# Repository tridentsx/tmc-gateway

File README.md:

# tmc-gateway

A PoE Ethernet- and USB-attached GPIB instrument gateway: one small board,
plugged directly into an instrument's IEEE-488 connector, that exposes it to
the network and to USB simultaneously.

## What it does

One RP2354A-based adapter per GPIB instrument, acting as that instrument's
GPIB System Controller and Controller-in-Charge, reachable over:

- **[HiSLIP][hislip]** (IVI-6.1) over Ethernet/PoE, TCP port 4880
- **USBTMC** and its **USB488** subclass over USB
- Raw SCPI over TCP port 5025 (planned; not yet built)

The central architectural rule, carried over from the design specification:

> HiSLIP, USBTMC/USB488, raw SCPI, and any future management interface never
> manipulate GPIB pins directly. They submit operations to one serialized
> GPIB engine.

That engine is [`gpib.Instrument`](gpib/instrument.go) — see
[Software](#software) below.

## Hardware

| | |
|---|---|
| MCU | RP2354A (RP2350 family, 2 MB integrated flash), QFN-60 |
| Ethernet | WIZnet W5500 (SPI) |
| PoE | DP9900LPB isolated PD module, IEEE 802.3af, with a USB-C alternate power path (§30.1) |
| GPIB transceivers | TI SN75160B (data bus) + SN75161B (management bus) |
| GPIB connector | 24-pin IEEE-488, NorComp 112-024-113R001 |
| USB | USB-C (USBTMC/USB488, plus alternate power input) |

Board is 62×68 mm, 4 copper layers. Schematic is complete and verified —
confirmed by actually running the checks below, not just citing an old note:
`scripts/netlist-check.py` reports **124 checks, 0 failures**; ERC reports 3
`pin_not_driven` errors, all on W5500 (`U2`) SPI inputs (`SCS`/`SCLK`/`MOSI`)
flagged because the driving RP2354A pins are bidirectional across a
hierarchical sheet link — a severity-policy question, not a wiring defect.
PCB has all 93 footprints placed but is **not yet routed**.

- [`docs/design-spec.md`](docs/design-spec.md) — the master design
  specification. One document by design: Part I is the HiSLIP library
  ([tridentsx/hislip][hislip], developed in that separate repository), Part
  II is this hardware, Part III is this firmware, and Parts IV–VII
  (milestones, acceptance criteria, design decisions, risk register) span
  all three. Source comments in `hislip` cite it by section, e.g. "§5.1".
- [`docs/netlist-spec.md`](docs/netlist-spec.md) / [`docs/netlist-spec.nets`](docs/netlist-spec.nets) —
  the canonical net table `scripts/netlist-check.py` verifies the exported
  schematic netlist against.
- [`docs/rp2354a-pinmap.md`](docs/rp2354a-pinmap.md) — the RP2354A GPIO
  assignment: 8 data lines and the DAV/NDAC/NRFD handshake lines suggested
  for PIO, ATN/SRQ/REN/IFC/EOI as plain GPIO, SPI0 to the W5500.

## Software

```text
gpib/            the Instrument abstraction every front end drives (no
                  firmware, no bus driver -- just the interface)
hislipfront/      adapts gpib.Instrument to tridentsx/hislip's server.Device
usbtmcfront/      adapts gpib.Instrument to USBTMC/USB488 Bulk-OUT messages
usbep/            portable, unit-tested USB packet reassembly (host->device)
                  and chunking (device->host) usbtmcfront's messages ride on
cmd/firmware/     the real (skeleton) RP2354A firmware entry point --
                  tinygo-only, gated by the "tinygo" build tag
cmd/tinygocheck/  not firmware -- exists so `just tinygo` has a real main
                  package to build and link, exercising gpib/hislipfront/
                  usbtmcfront together under mainline go's dependency
                  graph but a real tinygo build
cmd/debugconsole/ host-side only (plain go build, no tinygo tag): a
                  terminal UI for cmd/firmware's CDC debug console
```

`gpib.Instrument` is deliberately not a copy of `hislip/server.Device`,
despite both stating the identical "must not know it's GPIB" principle:
`RemoteEnable`, `LocalLockout`, and `GoToLocal` are three separate methods
here, because USB488's own control requests (`REN_CONTROL`, `GO_TO_LOCAL`,
`LOCAL_LOCKOUT`) are three separate requests, not HiSLIP's one combined
`RemoteLocal(mode)` call. Both front ends translate onto the same granular
primitives instead of one needing to reconstruct a combined mode it never
actually received.

### Status

| Piece | State |
|---|---|
| `gpib.Instrument` abstraction | Defined |
| `hislipfront` (HiSLIP → `gpib.Instrument`) | Implemented, unit-tested |
| `usbtmcfront` (USBTMC/USB488 → `gpib.Instrument`) | Core Bulk-OUT dispatch implemented, unit-tested — see scope below |
| `usbep` (USB packet reassembly/chunking) | Implemented, unit-tested — real edge cases (exact-multiple-of-packet-size, empty message, byte-at-a-time feed) |
| `cmd/firmware` (real USB descriptor + endpoint wiring) | Skeleton exists and **actually builds**: `tinygo build -target=pico2` produces a real, well-formed flashable UF2. Backed by a stub `gpib.Instrument` — no real GPIB bus driver yet. **Verified on real hardware** (a W5500-EVB-Pico2, RP2350): descriptor enumerates exactly as designed, and a real USBTMC `RequestDevDepMsgIn` round trip over EP3 OUT/IN produces a correctly encoded response — see below. |
| GPIB bus driver (the concrete `gpib.Instrument`) | Not started |
| Raw SCPI front end | Not started |

Real, load-bearing constraints found by reading TinyGo 0.42.0's actual
`machine/usb` source (not assumed): it hardcodes a **maximum of 3 USB
interfaces total** (a fixed-size array, not a slice), so a USB CDC debug
console (2 interfaces) plus USBTMC (1) exactly fills the budget, with no
room left for anything else on this port. Its outgoing-transfer path does
not itself split a payload larger than one packet across multiple
packets — that's what `usbep.ChunkSender` and `cmd/firmware`'s
`TxHandler` callback do, deliberately, rather than being handled for free
by the framework.

`usbtmcfront`'s stated scope, deliberately not (yet) covered:

- Works on one already-reassembled logical USBTMC message, not raw USB
  transfers — splitting a message across several USB packets and the
  alignment padding USBTMC requires between messages is a transport-framing
  concern for whatever wires it to a real USB endpoint later, the same
  split `hislip/server`'s `Stream` abstraction makes.
- TermChar-based early read termination is decoded but ignored.
- Every control-transfer-based USBTMC/USB488 request — `GET_CAPABILITIES`,
  `INITIATE_CLEAR`, `READ_STATUS_BYTE`, `REN_CONTROL`, `GO_TO_LOCAL`,
  `LOCAL_LOCKOUT`, the abort requests — is not implemented at all; only the
  three Bulk-OUT message types (`DevDepMsgOut`, `RequestDevDepMsgIn`,
  `Trigger`) are.

One real, non-mechanical piece of protocol work is still open before the
bus driver can start: **the real IEEE-488.1 three-wire handshake and
ATN-based addressing.** Nothing here has been verified against real GPIB
hardware yet; treat any bus-timing claim in this repo's history as reasoned
from the spec text, not measured.

### Real-hardware findings (`cmd/firmware`, W5500-EVB-Pico2 / RP2350)

Confirmed by actually flashing and exercising the board, not just building
for it:

- The composed descriptor (CDC debug console + USBTMC/USB488) enumerates
  exactly as designed: 3 interfaces, correct classes (CDC `0x02/0x02/0x01`
  + `0x0A/0x00/0x00`, USBTMC/USB488 `0xFE/0x03/0x01`), correct endpoint
  addresses (`0x03`/`0x83` for the shared USBTMC bulk endpoint).
- A real `RequestDevDepMsgIn` Bulk-OUT write followed by a Bulk-IN read,
  issued from the host with [go-usb][go-usb], round-trips correctly end to
  end through `usbtmcRxHandler` → `usbep.Reassembler` → `usbtmcfront.Handler`
  → `usbep.ChunkSender` → `usbtmcTxHandler`.
- Two real firmware bugs were found and fixed this way, both specific to
  running inside TinyGo's bare-metal USB interrupt handlers, not to the
  protocol logic itself:
  1. `main()` called `machine.EnableCDC` a second time. TinyGo's own
     runtime (`initUSB`, which runs before `main`) already calls it via
     `machine/usb/cdc.EnableUSBCDC` with working handlers; the redundant
     call overwrote them with no-op stubs, silently breaking the debug
     console.
  2. `usbtmcRxHandler` called `println`, `reasm.Feed`, `append`, and
     `usbtmcfront.Handler.HandleBulkOut` directly — all either blocking or
     allocating — from inside a USB interrupt handler. TinyGo's bare-metal
     allocator is not interrupt-safe, so this corrupted state the moment a
     real bulk transfer arrived. The handler now only copies the raw
     packet into a fixed-size ring with a plain array copy (no allocation,
     no blocking); reassembly, dispatch, and response encoding all run in
     the main loop instead, which drains that ring alongside a lightweight
     event log and a heartbeat print, giving an unambiguous liveness signal
     during this kind of debugging.

Built for the *next* real-hardware session, not just this one:
`cmd/firmware`'s CDC console is now interactive (`help`/`version`/
`stats`/`last`/`clear`/`uptime`/`ping`), backed by persistent counters
(packets in, messages reassembled, responses sent, ring overflows, TX
failures) and a bounded hex dump of the last message/response — confirmed
working on real hardware, including the counters incrementing correctly
across a real bulk transfer and `last` showing the exact bytes exchanged.
See `cmd/firmware/debug.go`. `version` reports the exact git commit (plus
`-dirty` if built from an uncommitted tree) and build time, baked in by
`just firmware`'s `-ldflags -X`, so it's possible to confirm which build
is actually running on a given board.

**`cmd/debugconsole`** is the host-side companion: a terminal UI
(`go run ./cmd/debugconsole`, or `just debugconsole`) with a menu of the
commands above plus a free-text box for anything not in that list yet,
so a real-hardware session doesn't mean hand-typing into `screen`/
`picocom`/a pyserial script. Plain `go build`, no `tinygo` tag — runs on
the development machine against an already-flashed, already-connected
board, never on the RP2350 itself.

## Related repositories

- [tridentsx/hislip][hislip] — the HiSLIP protocol/server/client library
  this board's Ethernet-side front end is built on. Intended, once
  finished, to be offered to the `gotmc` organisation.
- [tridentsx/usbtmc][usbtmc] — a fork of [gotmc/usbtmc][gotmc-usbtmc]
  adding a driver backed by [tridentsx/go-usb][go-usb] (no cgo, no
  libusb), intended to be contributed upstream. Its new `wire` subpackage
  is the USBTMC wire-format vocabulary this board's USB-side front end
  will build on.
- [tridentsx/go-usb][go-usb] — the pure-Go USB backend behind the
  `usbtmc` driver above.

## Building what exists today

```sh
go build ./...
go vet ./...
go test ./...
```

```sh
kicad-cli sch export netlist --format kicadsexpr -o build/adapter.net hardware/adapter.kicad_sch
python3 scripts/netlist-check.py docs/netlist-spec.nets build/adapter.net   # expect 131/0
kicad-cli sch erc --severity-error -o /tmp/erc.rpt hardware/adapter.kicad_sch
```

[hislip]: https://github.com/tridentsx/hislip
[usbtmc]: https://github.com/tridentsx/usbtmc
[gotmc-usbtmc]: https://github.com/gotmc/usbtmc
[go-usb]: https://github.com/tridentsx/go-usb

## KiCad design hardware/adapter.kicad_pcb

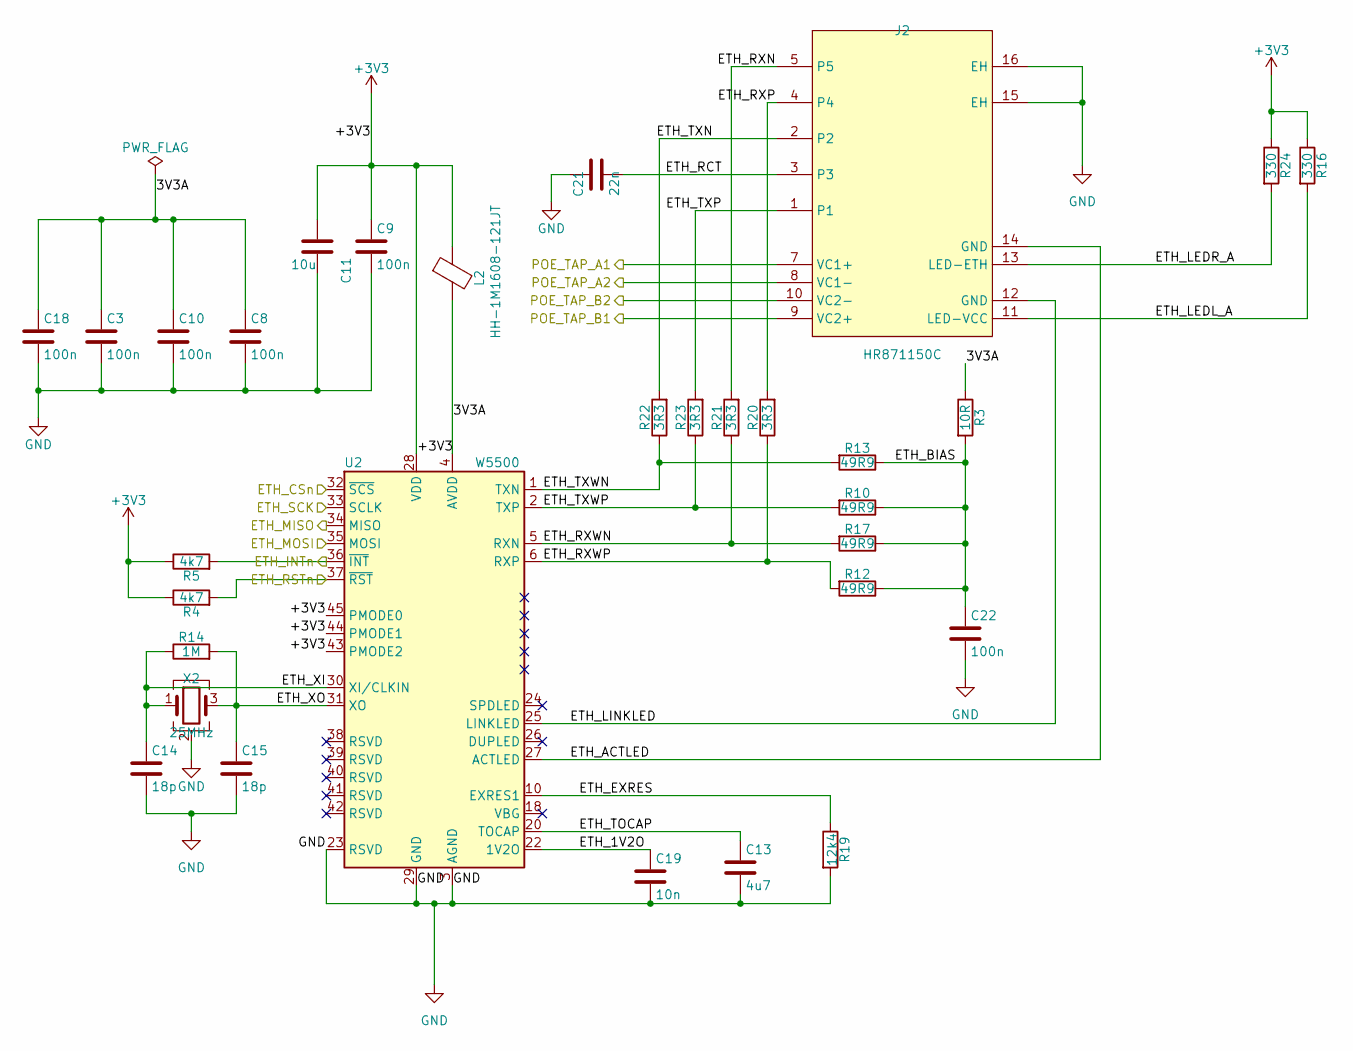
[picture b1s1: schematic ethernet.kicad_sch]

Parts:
C3, C8, C9, C10, C18, C22: 100n; C_0805_2012Metric
C11: 10u; C_0805_2012Metric
C13: 4u7; C_0805_2012Metric
C14, C15: 18p; C_0805_2012Metric
C19: 10n; C_0805_2012Metric; LCSC C1710
C21: 22n; C_0805_2012Metric
J2: HR871150C; RJ45-TH_HR871150C; LCSC C19724786
L2: HH-1M1608-121JT; L_0603_1608Metric
R3: 10R; R_0805_2012Metric
R4, R5: 4k7; R_0805_2012Metric
R10, R12, R13, R17: 49R9; R_0805_2012Metric
R14: 1M; R_0805_2012Metric
R16, R24: 330; R_0805_2012Metric
R19: 12k4; R_0805_2012Metric
R20, R21, R22, R23: 3R3; R_0805_2012Metric
U2: W5500; LQFP-48_7x7mm_P0.5mm; LCSC C32843
X2: 25MHz; Crystal_SMD_3225-4Pin_3.2x2.5mm; MPN X322525MOB4SI; LCSC Part C9006

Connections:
+3V3: C9.1, C11.1, L2.1, R4.1, R5.1, R16.1, R24.1, U2.28 (VDD), U2.43 (PMODE2), U2.44 (PMODE1), U2.45 (PMODE0); also elsewhere on the board
/Ethernet W5500 and magjack/3V3A: C3.1, C8.1, C10.1, C18.1, L2.2, R3.1, U2.4 (AVDD), U2.8 (AVDD), U2.11 (AVDD), U2.15 (AVDD), U2.17 (AVDD), U2.21 (AVDD)
/Ethernet W5500 and magjack/ETH_1V2O: C19.1, U2.22 (1V2O)
/Ethernet W5500 and magjack/ETH_ACTLED: J2.14 (GND), U2.27 (ACTLED)
/Ethernet W5500 and magjack/ETH_BIAS: C22.1, R3.2, R10.1, R12.1, R13.1, R17.1
/Ethernet W5500 and magjack/ETH_CSn: U2.32 (~SCS); also elsewhere on the board
/Ethernet W5500 and magjack/ETH_EXRES: R19.1, U2.10 (EXRES1)
/Ethernet W5500 and magjack/ETH_INTn: R5.2, U2.36 (~INT); also elsewhere on the board
/Ethernet W5500 and magjack/ETH_LEDL_A: J2.11 (LED-VCC), R16.2
/Ethernet W5500 and magjack/ETH_LEDR_A: J2.13 (LED-ETH), R24.2
/Ethernet W5500 and magjack/ETH_LINKLED: J2.12 (GND), U2.25 (LINKLED)
/Ethernet W5500 and magjack/ETH_MISO: U2.34 (MISO); also elsewhere on the board
/Ethernet W5500 and magjack/ETH_MOSI: U2.35 (MOSI); also elsewhere on the board
/Ethernet W5500 and magjack/ETH_RCT: C21.1, J2.3
/Ethernet W5500 and magjack/ETH_RSTn: R4.2, U2.37 (~RST); also elsewhere on the board
/Ethernet W5500 and magjack/ETH_RXN: J2.5, R21.2
/Ethernet W5500 and magjack/ETH_RXP: J2.4, R20.2
/Ethernet W5500 and magjack/ETH_RXWN: R17.2, R21.1, U2.5 (RXN)
/Ethernet W5500 and magjack/ETH_RXWP: R12.2, R20.1, U2.6 (RXP)
/Ethernet W5500 and magjack/ETH_SCK: U2.33 (SCLK); also elsewhere on the board
/Ethernet W5500 and magjack/ETH_TOCAP: C13.1, U2.20 (TOCAP)
/Ethernet W5500 and magjack/ETH_TXN: J2.2, R22.2
/Ethernet W5500 and magjack/ETH_TXP: J2.1, R23.2
/Ethernet W5500 and magjack/ETH_TXWN: R13.2, R22.1, U2.1 (TXN)
/Ethernet W5500 and magjack/ETH_TXWP: R10.2, R23.1, U2.2 (TXP)
/Ethernet W5500 and magjack/ETH_XI: C14.1, R14.1, U2.30 (XI/CLKIN), X2.1
/Ethernet W5500 and magjack/ETH_XO: C15.1, R14.2, U2.31 (XO), X2.3
/Ethernet W5500 and magjack/POE_TAP_A1: J2.7 (VC1+); also elsewhere on the board
/Ethernet W5500 and magjack/POE_TAP_A2: J2.8 (VC1-); also elsewhere on the board
/Ethernet W5500 and magjack/POE_TAP_B1: J2.9 (VC2+); also elsewhere on the board
/Ethernet W5500 and magjack/POE_TAP_B2: J2.10 (VC2-); also elsewhere on the board

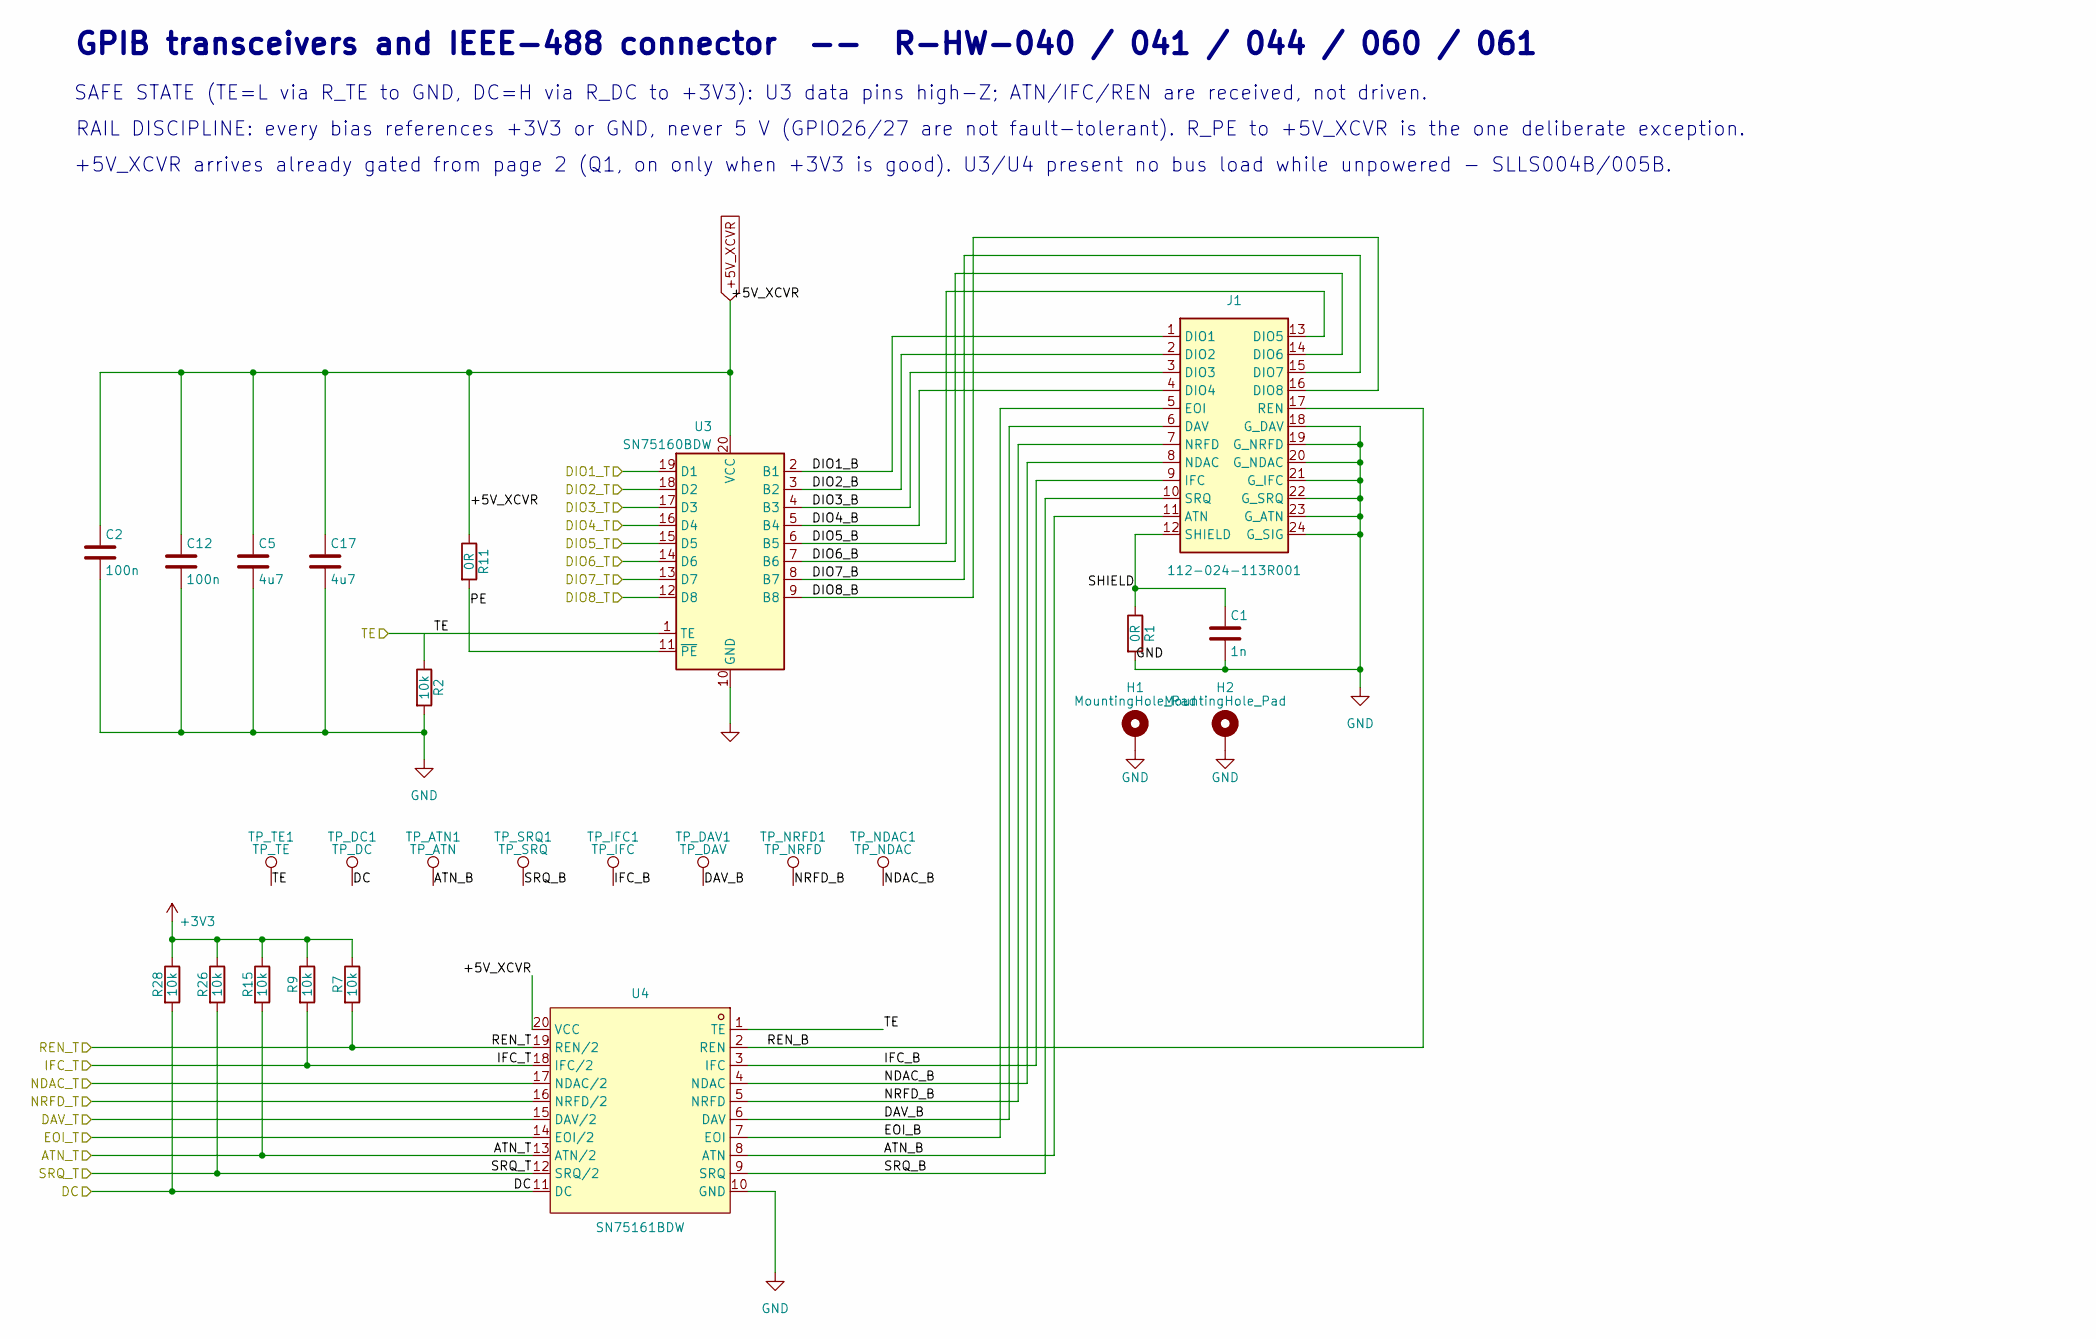
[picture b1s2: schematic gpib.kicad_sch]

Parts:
C1: 1n; C_0805_2012Metric
C2, C12: 100n; C_0805_2012Metric; LCSC C49678
C5, C17: 4u7; C_0805_2012Metric; LCSC C1779
H1, H2: MountingHole_Pad; MountingHole_3.2mm_M3_Pad
J1: 112-024-113R001; CONN_112-024-113R001_NRC; MPN 112-024-113R001
R1, R11: 0R; R_0805_2012Metric
R2: 10k; R_0805_2012Metric; LCSC C17414
R7, R9, R15, R26, R28: 10k; R_0805_2012Metric
TP_ATN1: TP_ATN; TestPoint_Pad_D1.5mm
TP_DAV1: TP_DAV; TestPoint_Pad_D1.5mm
TP_DC1: TP_DC; TestPoint_Pad_D1.5mm
TP_IFC1: TP_IFC; TestPoint_Pad_D1.5mm
TP_NDAC1: TP_NDAC; TestPoint_Pad_D1.5mm
TP_NRFD1: TP_NRFD; TestPoint_Pad_D1.5mm
TP_SRQ1: TP_SRQ; TestPoint_Pad_D1.5mm
TP_TE1: TP_TE; TestPoint_Pad_D1.5mm
U3: SN75160BDW; SOIC-20W_7.5x12.8mm_P1.27mm
U4: SN75161BDW; SOIC-20W_7.5x12.8mm_P1.27mm; LCSC C139410

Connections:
+3V3: R7.1, R9.1, R15.1, R26.1, R28.1; also elsewhere on the board
/GPIB transceivers and IEEE-488 connector/ATN_B: J1.11 (ATN), TP_ATN1.1 (1_1), U4.8 (ATN)
/GPIB transceivers and IEEE-488 connector/ATN_T: R15.2, U4.13 (ATN/2); also elsewhere on the board
/GPIB transceivers and IEEE-488 connector/DAV_B: J1.6 (DAV), TP_DAV1.1 (1_1), U4.6 (DAV)
/GPIB transceivers and IEEE-488 connector/DAV_T: U4.15 (DAV/2); also elsewhere on the board
/GPIB transceivers and IEEE-488 connector/DC: R28.2, TP_DC1.1 (1_1), U4.11 (DC); also elsewhere on the board
/GPIB transceivers and IEEE-488 connector/DIO1_B: J1.1 (DIO1), U3.2 (B1)
/GPIB transceivers and IEEE-488 connector/DIO1_T: U3.19 (D1); also elsewhere on the board
/GPIB transceivers and IEEE-488 connector/DIO2_B: J1.2 (DIO2), U3.3 (B2)
/GPIB transceivers and IEEE-488 connector/DIO2_T: U3.18 (D2); also elsewhere on the board
/GPIB transceivers and IEEE-488 connector/DIO3_B: J1.3 (DIO3), U3.4 (B3)
/GPIB transceivers and IEEE-488 connector/DIO3_T: U3.17 (D3); also elsewhere on the board
/GPIB transceivers and IEEE-488 connector/DIO4_B: J1.4 (DIO4), U3.5 (B4)
/GPIB transceivers and IEEE-488 connector/DIO4_T: U3.16 (D4); also elsewhere on the board
/GPIB transceivers and IEEE-488 connector/DIO5_B: J1.13 (DIO5), U3.6 (B5)
/GPIB transceivers and IEEE-488 connector/DIO5_T: U3.15 (D5); also elsewhere on the board
/GPIB transceivers and IEEE-488 connector/DIO6_B: J1.14 (DIO6), U3.7 (B6)
/GPIB transceivers and IEEE-488 connector/DIO6_T: U3.14 (D6); also elsewhere on the board
/GPIB transceivers and IEEE-488 connector/DIO7_B: J1.15 (DIO7), U3.8 (B7)
/GPIB transceivers and IEEE-488 connector/DIO7_T: U3.13 (D7); also elsewhere on the board
/GPIB transceivers and IEEE-488 connector/DIO8_B: J1.16 (DIO8), U3.9 (B8)
/GPIB transceivers and IEEE-488 connector/DIO8_T: U3.12 (D8); also elsewhere on the board
/GPIB transceivers and IEEE-488 connector/EOI_B: J1.5 (EOI), U4.7 (EOI)
/GPIB transceivers and IEEE-488 connector/EOI_T: U4.14 (EOI/2); also elsewhere on the board
/GPIB transceivers and IEEE-488 connector/IFC_B: J1.9 (IFC), TP_IFC1.1 (1_1), U4.3 (IFC)
/GPIB transceivers and IEEE-488 connector/IFC_T: R9.2, U4.18 (IFC/2); also elsewhere on the board
/GPIB transceivers and IEEE-488 connector/NDAC_B: J1.8 (NDAC), TP_NDAC1.1 (1_1), U4.4 (NDAC)
/GPIB transceivers and IEEE-488 connector/NDAC_T: U4.17 (NDAC/2); also elsewhere on the board
/GPIB transceivers and IEEE-488 connector/NRFD_B: J1.7 (NRFD), TP_NRFD1.1 (1_1), U4.5 (NRFD)
/GPIB transceivers and IEEE-488 connector/NRFD_T: U4.16 (NRFD/2); also elsewhere on the board
/GPIB transceivers and IEEE-488 connector/PE: R11.2, U3.11 (~PE)
/GPIB transceivers and IEEE-488 connector/REN_B: J1.17 (REN), U4.2 (REN)
/GPIB transceivers and IEEE-488 connector/REN_T: R7.2, U4.19 (REN/2); also elsewhere on the board
/GPIB transceivers and IEEE-488 connector/SHIELD: C1.1, J1.12 (SHIELD), R1.1
/GPIB transceivers and IEEE-488 connector/SRQ_B: J1.10 (SRQ), TP_SRQ1.1 (1_1), U4.9 (SRQ)
/GPIB transceivers and IEEE-488 connector/SRQ_T: R26.2, U4.12 (SRQ/2); also elsewhere on the board
/GPIB transceivers and IEEE-488 connector/TE: R2.1, TP_TE1.1 (1_1), U3.1 (TE), U4.1 (TE); also elsewhere on the board

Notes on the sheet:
RAIL DISCIPLINE: every bias references +3V3 or GND, never 5 V (GPIO26/27 are not fault-tolerant). R_PE to +5V_XCVR is the one deliberate exception.
+5V_XCVR arrives already gated from page 2 (Q1, on only when +3V3 is good). U3/U4 present no bus load while unpowered - SLLS004B/005B.
SAFE STATE (TE=L via R_TE to GND, DC=H via R_DC to +3V3): U3 data pins high-Z; ATN/IFC/REN are received, not driven.
GPIB transceivers and IEEE-488 connector -- R-HW-040 / 041 / 044 / 060 / 061

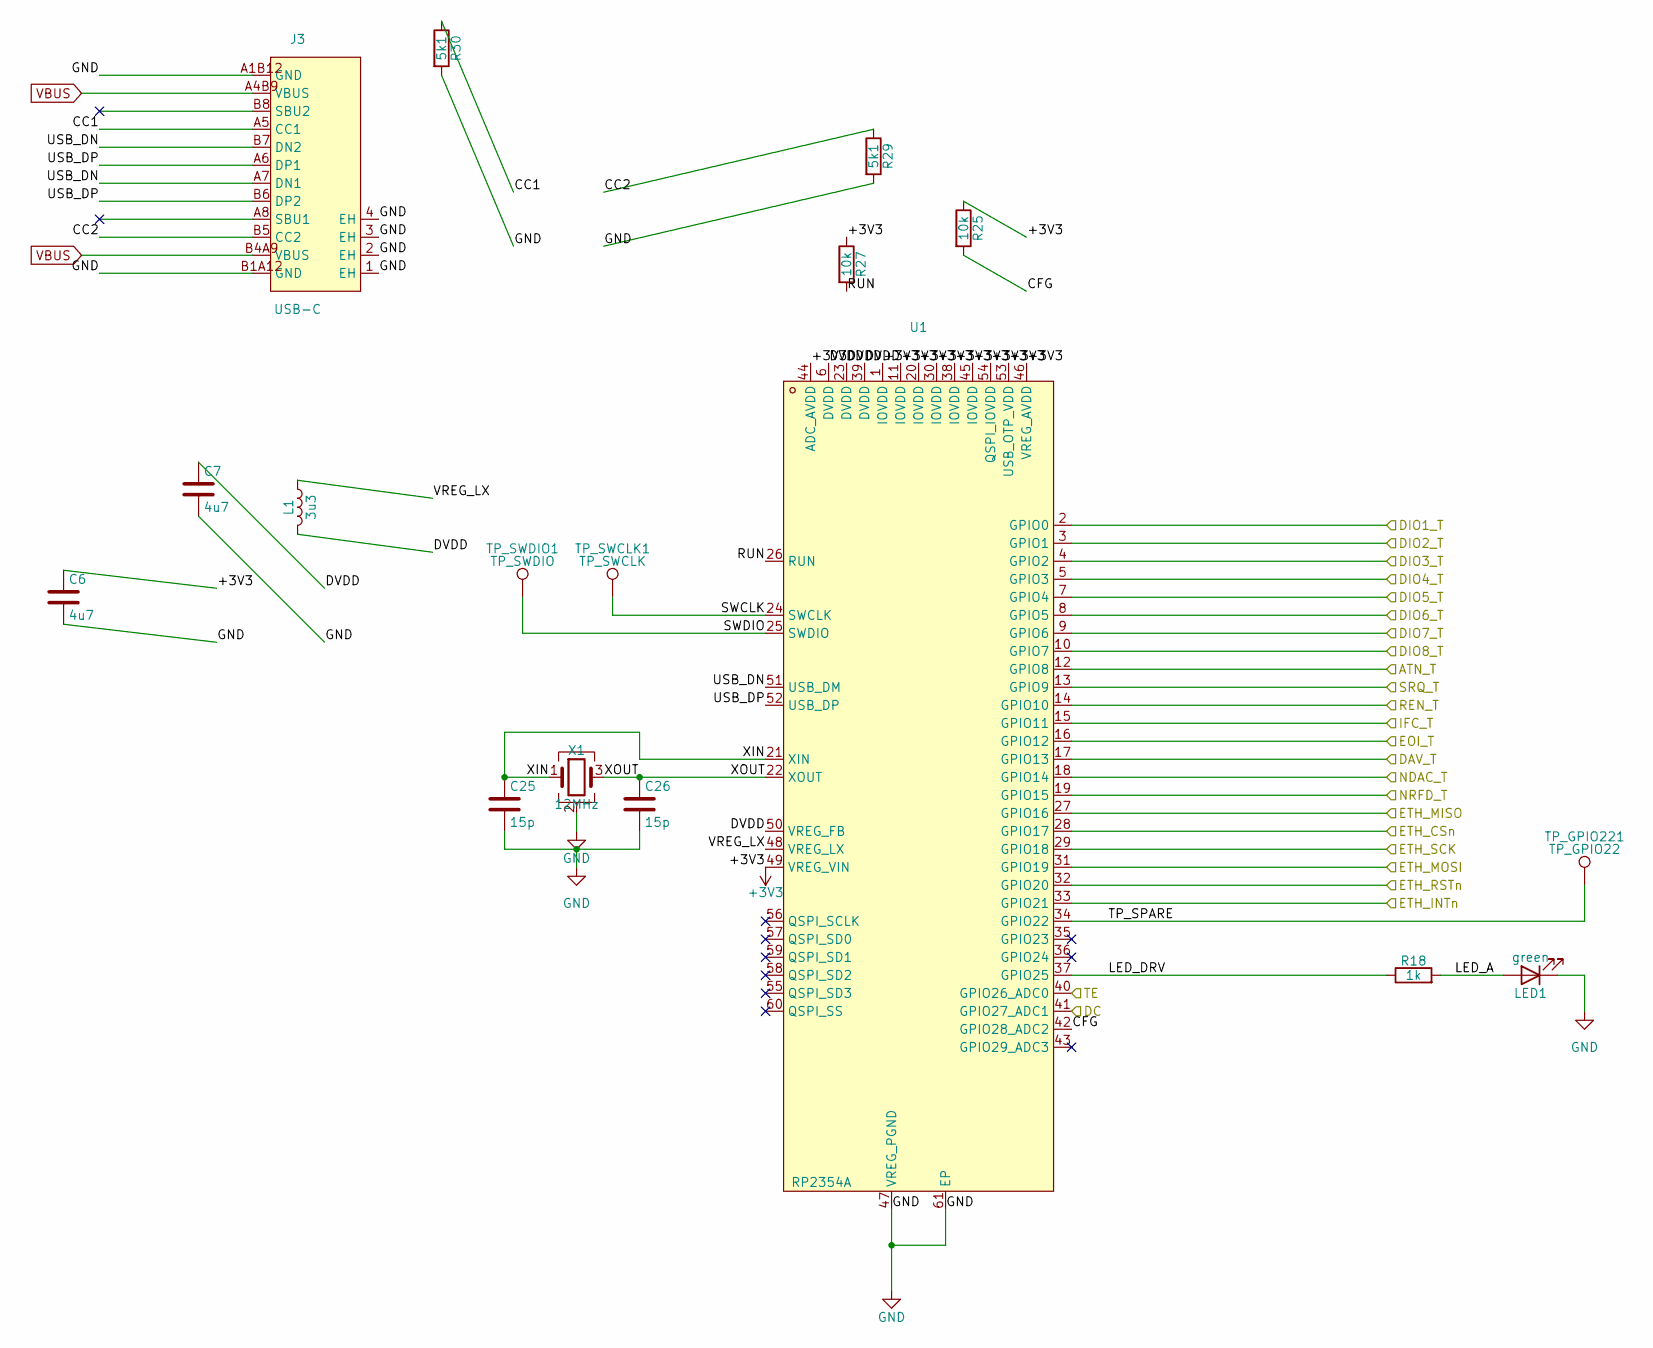
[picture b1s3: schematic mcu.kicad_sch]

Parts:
C6, C7: 4u7; C_0805_2012Metric
C25, C26: 15p; C_0805_2012Metric
J3: USB-C; USB-C_SMD-TYPE-C-31-M-12_1; LCSC C165948
L1: 3u3; L_0805_2012Metric
LED1: green; LED_0805_2012Metric
R18: 1k; R_0805_2012Metric
R25, R27: 10k; R_0805_2012Metric
R29, R30: 5k1; R_0805_2012Metric
TP_GPIO221: TP_GPIO22; TestPoint_Pad_D1.5mm
TP_SWCLK1: TP_SWCLK; TestPoint_Pad_D1.5mm
TP_SWDIO1: TP_SWDIO; TestPoint_Pad_D1.5mm
U1: RP2354A; QFN-60_L7.0-W7.0-P0.40-TL-EP3.4; LCSC C41378174
X1: 12MHz; Crystal_SMD_3225-4Pin_3.2x2.5mm; MPN CF4012M00012001; LCSC Part C7294550

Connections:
+3V3: C6.1, R25.1, R27.1, U1.1 (IOVDD), U1.11 (IOVDD), U1.20 (IOVDD), U1.30 (IOVDD), U1.38 (IOVDD), U1.44 (ADC_AVDD), U1.45 (IOVDD), U1.46 (VREG_AVDD), U1.49 (VREG_VIN), U1.53 (USB_OTP_VDD), U1.54 (QSPI_IOVDD); also elsewhere on the board
/Ethernet W5500 and magjack/ETH_CSn: U1.28 (GPIO17); also elsewhere on the board
/Ethernet W5500 and magjack/ETH_INTn: U1.33 (GPIO21); also elsewhere on the board
/Ethernet W5500 and magjack/ETH_MISO: U1.27 (GPIO16); also elsewhere on the board
/Ethernet W5500 and magjack/ETH_MOSI: U1.31 (GPIO19); also elsewhere on the board
/Ethernet W5500 and magjack/ETH_RSTn: U1.32 (GPIO20); also elsewhere on the board
/Ethernet W5500 and magjack/ETH_SCK: U1.29 (GPIO18); also elsewhere on the board
/GPIB transceivers and IEEE-488 connector/ATN_T: U1.12 (GPIO8); also elsewhere on the board
/GPIB transceivers and IEEE-488 connector/DAV_T: U1.17 (GPIO13); also elsewhere on the board
/GPIB transceivers and IEEE-488 connector/DC: U1.41 (GPIO27_ADC1); also elsewhere on the board
/GPIB transceivers and IEEE-488 connector/DIO1_T: U1.2 (GPIO0); also elsewhere on the board
/GPIB transceivers and IEEE-488 connector/DIO2_T: U1.3 (GPIO1); also elsewhere on the board
/GPIB transceivers and IEEE-488 connector/DIO3_T: U1.4 (GPIO2); also elsewhere on the board
/GPIB transceivers and IEEE-488 connector/DIO4_T: U1.5 (GPIO3); also elsewhere on the board
/GPIB transceivers and IEEE-488 connector/DIO5_T: U1.7 (GPIO4); also elsewhere on the board
/GPIB transceivers and IEEE-488 connector/DIO6_T: U1.8 (GPIO5); also elsewhere on the board
/GPIB transceivers and IEEE-488 connector/DIO7_T: U1.9 (GPIO6); also elsewhere on the board
/GPIB transceivers and IEEE-488 connector/DIO8_T: U1.10 (GPIO7); also elsewhere on the board
/GPIB transceivers and IEEE-488 connector/EOI_T: U1.16 (GPIO12); also elsewhere on the board
/GPIB transceivers and IEEE-488 connector/IFC_T: U1.15 (GPIO11); also elsewhere on the board
/GPIB transceivers and IEEE-488 connector/NDAC_T: U1.18 (GPIO14); also elsewhere on the board
/GPIB transceivers and IEEE-488 connector/NRFD_T: U1.19 (GPIO15); also elsewhere on the board
/GPIB transceivers and IEEE-488 connector/REN_T: U1.14 (GPIO10); also elsewhere on the board
/GPIB transceivers and IEEE-488 connector/SRQ_T: U1.13 (GPIO9); also elsewhere on the board
/GPIB transceivers and IEEE-488 connector/TE: U1.40 (GPIO26_ADC0); also elsewhere on the board
/MCU RP2354A/CC1: J3.A5 (CC1), R30.1
/MCU RP2354A/CC2: J3.B5 (CC2), R29.1
/MCU RP2354A/CFG: R25.2, U1.42 (GPIO28_ADC2)
/MCU RP2354A/DVDD: C7.1, L1.2, U1.6 (DVDD), U1.23 (DVDD), U1.39 (DVDD), U1.50 (VREG_FB)
/MCU RP2354A/LED_A: LED1.2 (A), R18.2
/MCU RP2354A/LED_DRV: R18.1, U1.37 (GPIO25)
/MCU RP2354A/RUN: R27.2, U1.26 (RUN)
/MCU RP2354A/SWCLK: TP_SWCLK1.1 (1_1), U1.24 (SWCLK)
/MCU RP2354A/SWDIO: TP_SWDIO1.1 (1_1), U1.25 (SWDIO)
/MCU RP2354A/TP_SPARE: TP_GPIO221.1 (1_1), U1.34 (GPIO22)
/MCU RP2354A/USB_DN: J3.A7 (DN1), J3.B7 (DN2), U1.51 (USB_DM)
/MCU RP2354A/USB_DP: J3.A6 (DP1), J3.B6 (DP2), U1.52 (USB_DP)
/MCU RP2354A/VREG_LX: L1.1, U1.48 (VREG_LX)
/MCU RP2354A/XIN: C25.1, U1.21 (XIN), X1.1
/MCU RP2354A/XOUT: C26.1, U1.22 (XOUT), X1.3
VBUS: J3.A4B9 (VBUS), J3.B4A9 (VBUS); also elsewhere on the board

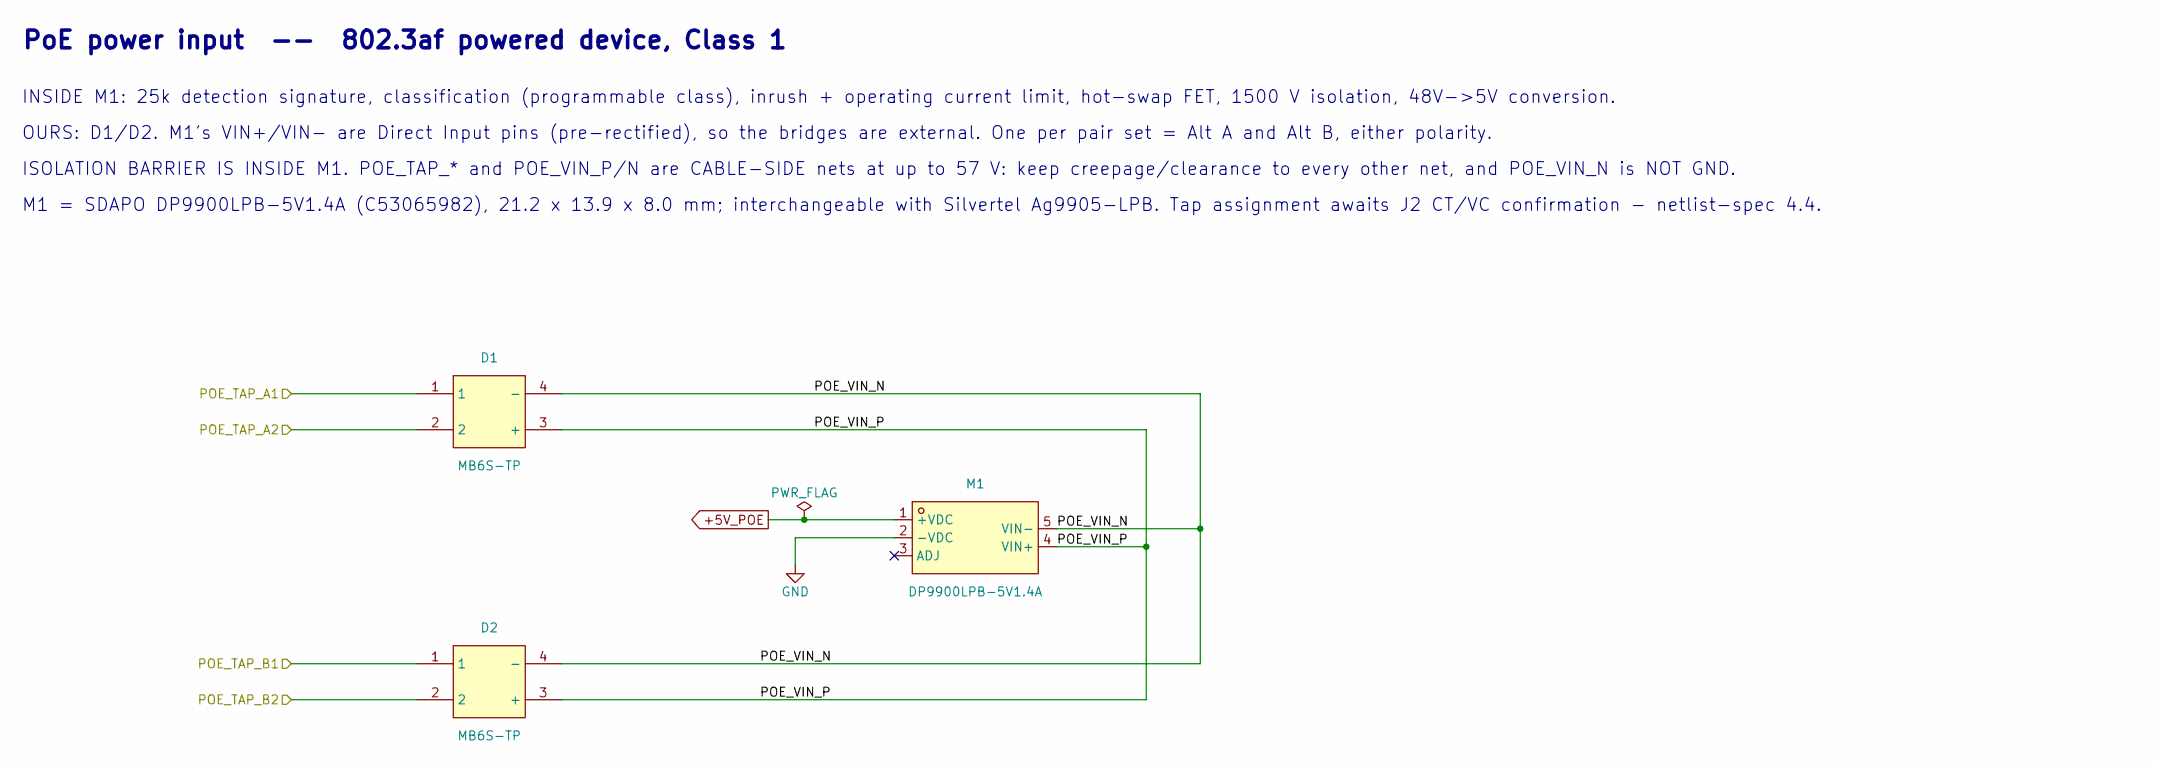
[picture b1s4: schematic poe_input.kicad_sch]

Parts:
D1, D2: MB6S-TP; MBS_L4.7-W4.0-P2.50-LS7.0-TL; LCSC C85619
M1: DP9900LPB-5V1.4A; COMM-SMD_DP9900LPB-5V1.4A; LCSC C53065982

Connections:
+5V_POE: M1.1 (+VDC); also elsewhere on the board
/Ethernet W5500 and magjack/POE_TAP_A1: D1.1; also elsewhere on the board
/Ethernet W5500 and magjack/POE_TAP_A2: D1.2; also elsewhere on the board
/Ethernet W5500 and magjack/POE_TAP_B1: D2.1; also elsewhere on the board
/Ethernet W5500 and magjack/POE_TAP_B2: D2.2; also elsewhere on the board
/PoE power input/POE_VIN_N: D1.4 (-), D2.4 (-), M1.5 (VIN-)
/PoE power input/POE_VIN_P: D1.3 (+), D2.3 (+), M1.4 (VIN+)

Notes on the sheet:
OURS: D1/D2. M1's VIN+/VIN- are Direct Input pins (pre-rectified), so the bridges are external. One per pair set = Alt A and Alt B, either polarity.
ISOLATION BARRIER IS INSIDE M1. POE_TAP_* and POE_VIN_P/N are CABLE-SIDE nets at up to 57 V: keep creepage/clearance to every other net, and POE_VIN_N is NOT GND.
M1 = SDAPO DP9900LPB-5V1.4A (C53065982), 21.2 x 13.9 x 8.0 mm; interchangeable with Silvertel Ag9905-LPB. Tap assignment awaits J2 CT/VC confirmation - netlist-spec 4.4.
INSIDE M1: 25k detection signature, classification (programmable class), inrush + operating current limit, hot-swap FET, 1500 V isolation, 48V->5V conversion.
PoE power input -- 802.3af powered device, Class 1

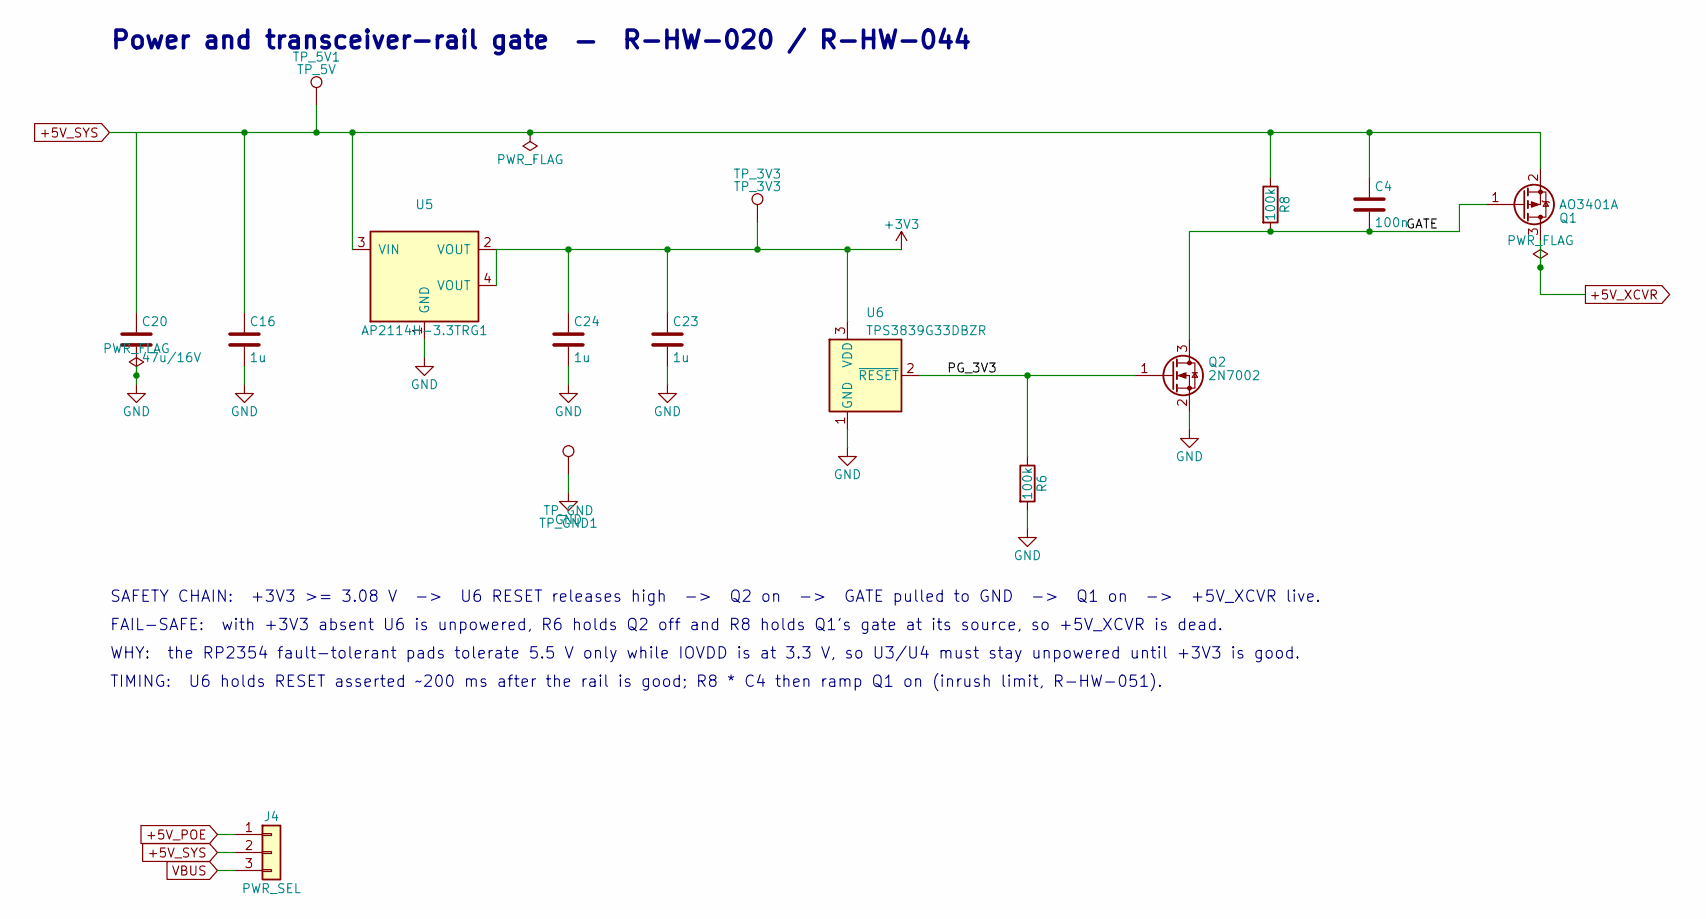
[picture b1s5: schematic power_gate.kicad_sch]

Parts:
C4: 100n; C_0805_2012Metric
C16, C24: 1u; C_0805_2012Metric
C20: 47u/16V; C_1206_3216Metric
C23: 1u; C_0805_2012Metric; LCSC C28323
J4: PWR_SEL; PinHeader_1x03_P2.54mm_Vertical
Q1: AO3401A; SOT-23; LCSC C15127
Q2: 2N7002; SOT-23; LCSC C8545
R6, R8: 100k; R_0805_2012Metric
TP_3V3: TP_3V3; TestPoint_Pad_D1.5mm
TP_5V1: TP_5V; TestPoint_Pad_D1.5mm
TP_GND1: TP_GND; TestPoint_Pad_D1.5mm
U5: AP2114H-3.3TRG1; SOT-223_L6.7-W3.5-P2.30-BR; LCSC C150716
U6: TPS3839G33DBZR; SOT-23; LCSC C485802

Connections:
+3V3: C23.1, C24.1, TP_3V3.1 (1_1), U5.2 (VOUT), U5.4 (VOUT), U6.3 (VDD); also elsewhere on the board
+5V_POE: J4.1; also elsewhere on the board
/Power and transceiver-rail gate/GATE: C4.2, Q1.1 (G), Q2.3 (D), R8.2
/Power and transceiver-rail gate/PG_3V3: Q2.1 (G), R6.1, U6.2 (~RESET)
VBUS: J4.3; also elsewhere on the board

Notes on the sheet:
FAIL-SAFE: with +3V3 absent U6 is unpowered, R6 holds Q2 off and R8 holds Q1's gate at its source, so +5V_XCVR is dead.
SAFETY CHAIN: +3V3 >= 3.08 V -> U6 RESET releases high -> Q2 on -> GATE pulled to GND -> Q1 on -> +5V_XCVR live.
TIMING: U6 holds RESET asserted ~200 ms after the rail is good; R8 * C4 then ramp Q1 on (inrush limit, R-HW-051).
WHY: the RP2354 fault-tolerant pads tolerate 5.5 V only while IOVDD is at 3.3 V, so U3/U4 must stay unpowered until +3V3 is good.
Power and transceiver-rail gate — R-HW-020 / R-HW-044

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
